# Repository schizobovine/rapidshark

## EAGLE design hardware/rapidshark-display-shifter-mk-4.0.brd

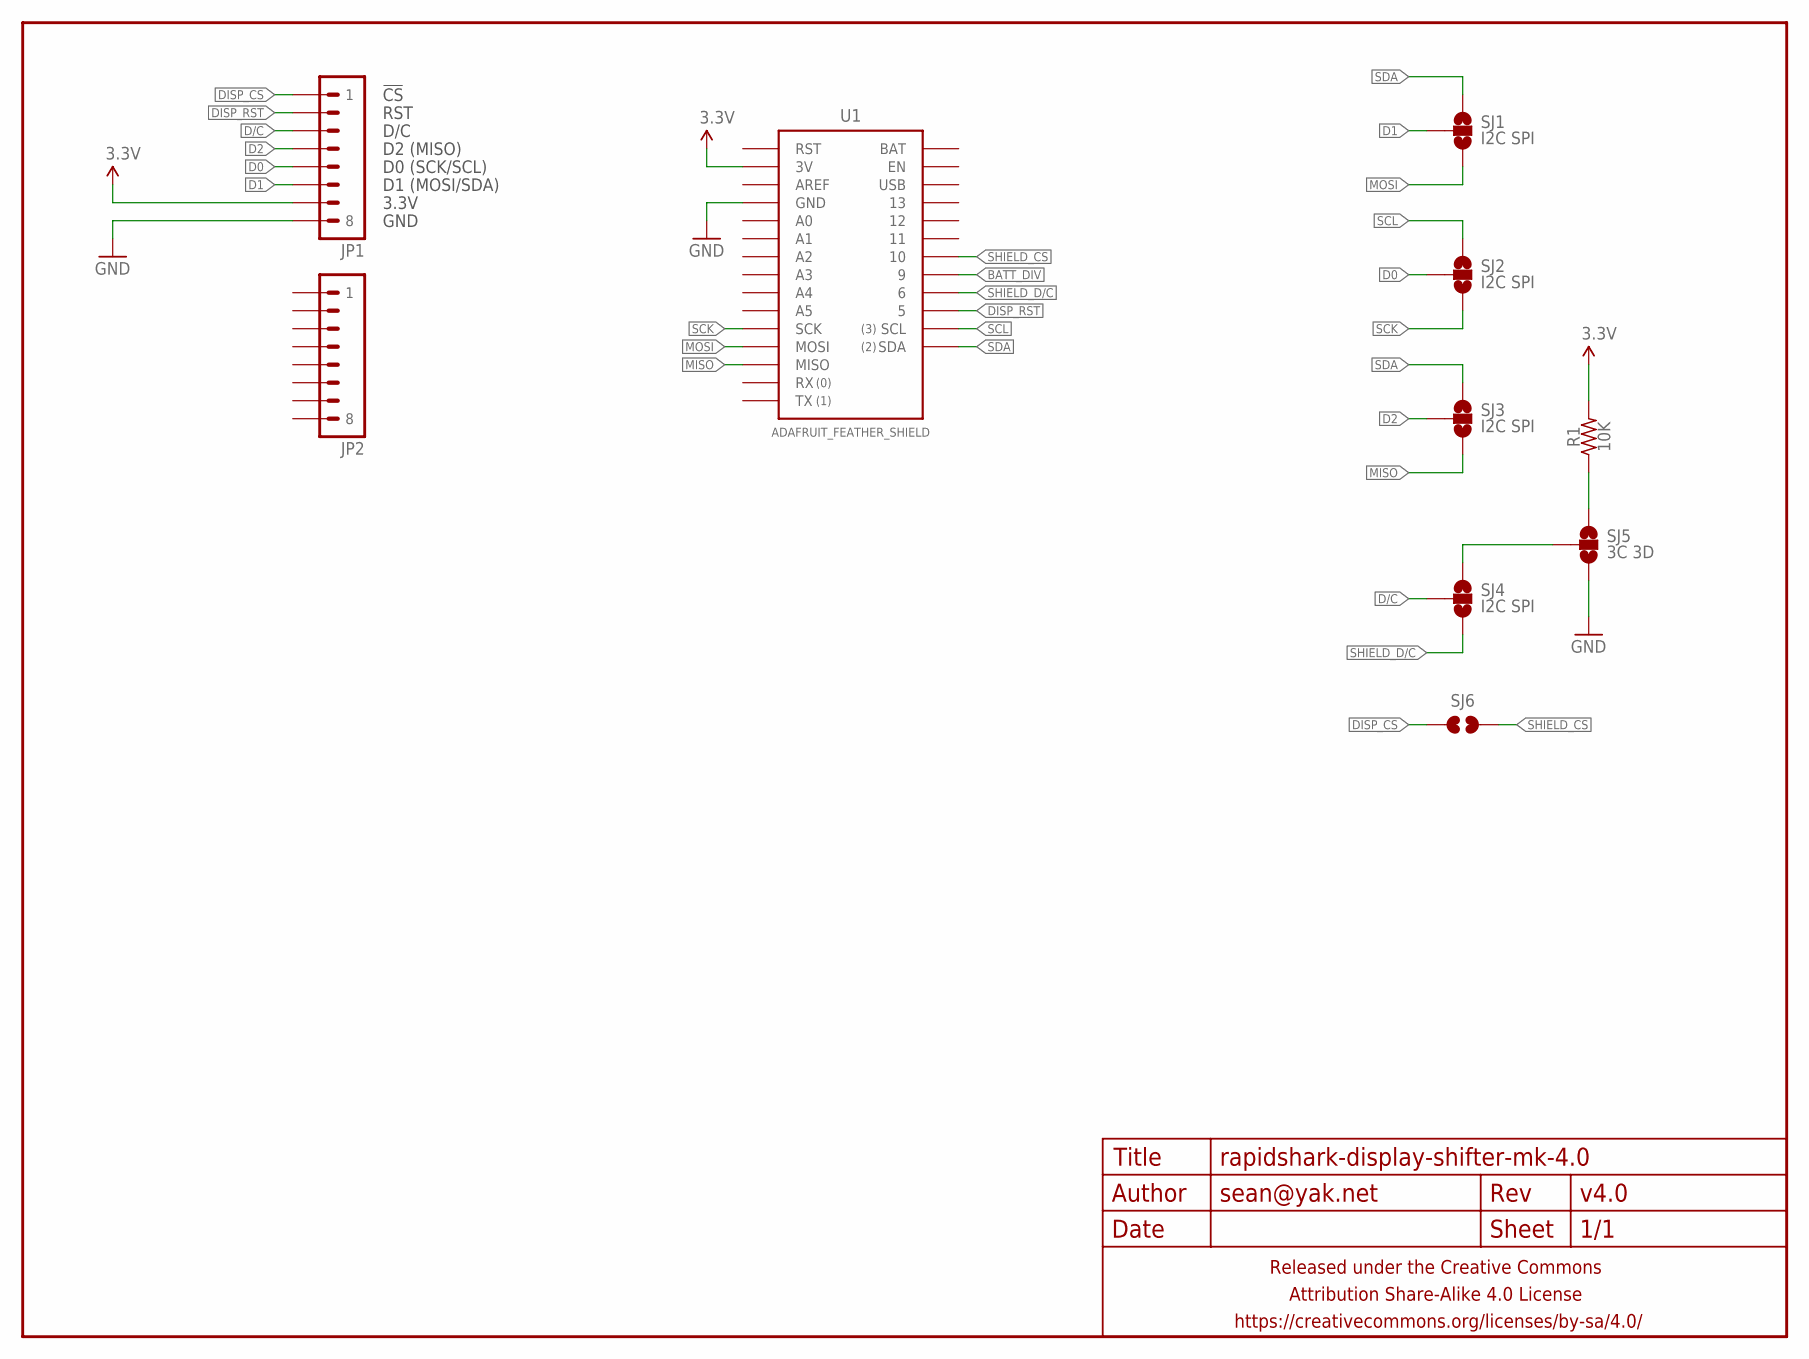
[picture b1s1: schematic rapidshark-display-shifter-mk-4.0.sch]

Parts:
FRAME1: FRAME-LETTERNO_PACKAGE; DUMMY
JP1, JP2: M081X08; 1X08
R1: 10K; R0603
SJ1, SJ2, SJ3, SJ4: I2C SPI; PAD-JUMPER-3-NO_YES_SILK_FULL_BOX
SJ5: 3C 3D; PAD-JUMPER-3-NO_YES_SILK_FULL_BOX
SJ6: JUMPER-PAD-2-NOYES_SILK; PAD-JUMPER-2-NO_YES_SILK
U1: ADAFRUIT_FEATHER_SHIELD; ADAFRUIT_FEATHER

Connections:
3.3V: JP1.7, R1.2, U1.3V
BATT_DIV: U1.9
D0: JP1.5, SJ2.2
D1: JP1.6
D2: JP1.4
D/C: JP1.3
DISP_CS: JP1.1, SJ6.1
DISP_RST: JP1.2, U1.5
GND: JP1.8, SJ5.3, U1.GND@0 (GND), U1.GND@1 (GND)
MISO: SJ3.3, U1.MISO
MOSI: SJ1.3, U1.MOSI
unnamed: R1.1, SJ5.1
unnamed: SJ4.1, SJ5.2
SCK: SJ2.3, U1.SCK
SCL: SJ2.1, U1.SCL
SDA: SJ1.1, U1.SDA
SHIELD_CS: SJ6.2, U1.10
SHIELD_D/C: SJ4.3, U1.6

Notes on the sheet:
GND
3.3V
D1 (MOSI/SDA)
D0 (SCK/SCL)
D2 (MISO)
D/C
RST
!CS

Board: 2 copper layers, 13 parts (3 on the bottom side), 14 nets, no tracks yet.

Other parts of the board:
U$1: COW_SMALL
U$3: OSHWLOGO_TINY_SILKONLY

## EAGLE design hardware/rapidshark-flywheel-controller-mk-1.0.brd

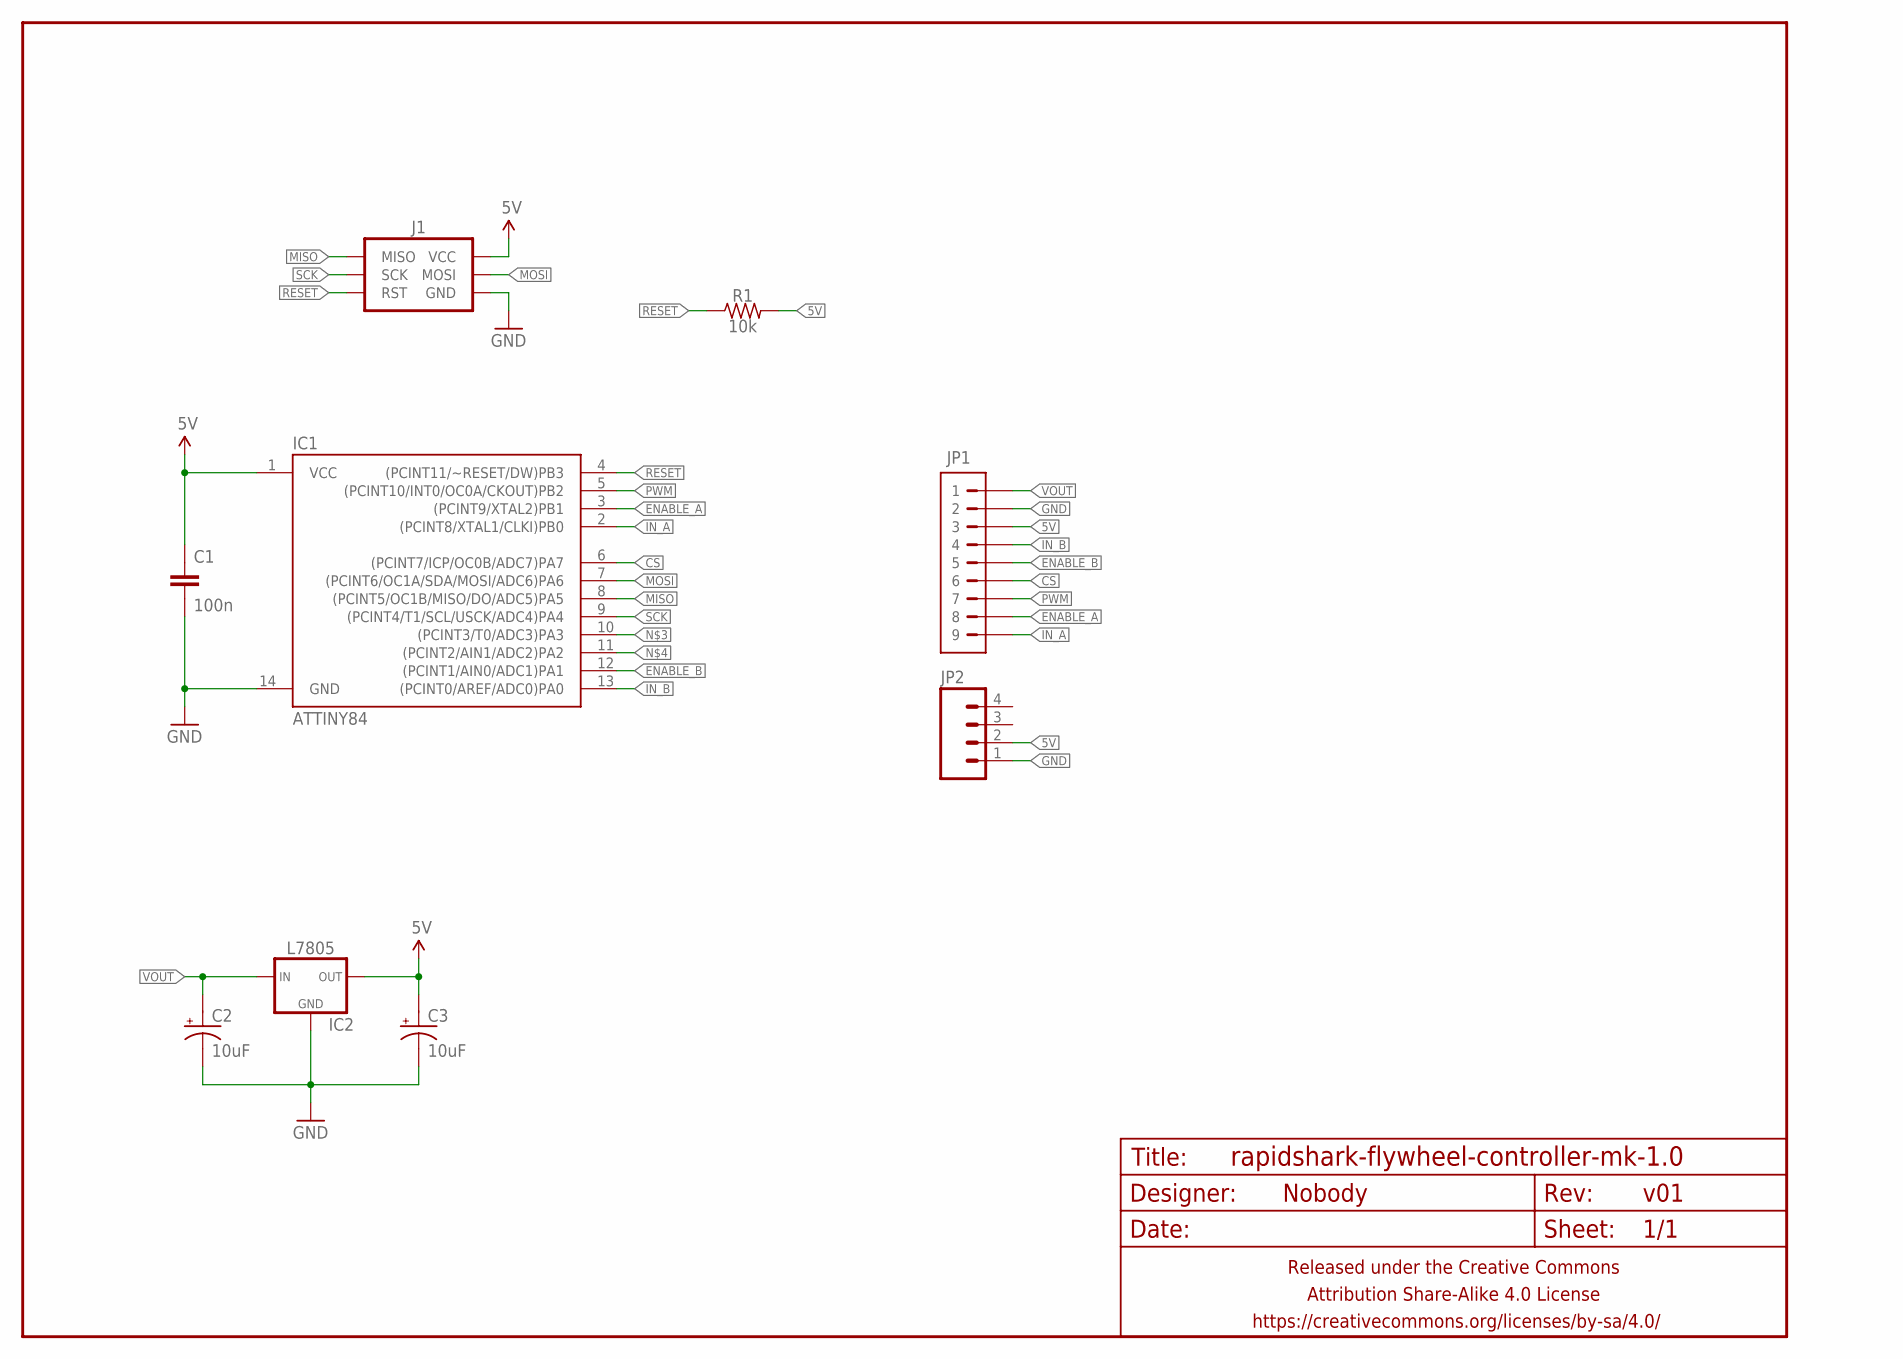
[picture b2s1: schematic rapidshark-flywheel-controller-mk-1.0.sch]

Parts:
C1: 100n; C0805
C2, C3: 10uF; E2-5
FRAME1: FRAME-LETTERNO_PACKAGE; DUMMY
IC1: ATTINY84; SO14
IC2: L7805; TO-92-AMMO
J1: AVR_SPI_PRG_6PTH; 2X3
JP1: M09CENTERED; 1X09-CENTERED
JP2: M04JST-PTH-VERT; JST-4-PH-VERT-PTH
R1: 10k; R0805

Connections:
5V: C1.1, C3.+, IC1.1 (VCC), IC2.3 (OUT), J1.2 (VCC), JP1.3, JP2.2, R1.2
CS: IC1.6 ((PCINT7/ICP/OC0B/ADC7)PA7), JP1.6
ENABLE_A: IC1.3 ((PCINT9/XTAL2)PB1), JP1.8
ENABLE_B: IC1.12 ((PCINT1/AIN0/ADC1)PA1), JP1.5
GND: C1.2, C2.-, C3.-, IC1.14 (GND), IC2.2 (GND), J1.6 (GND), JP1.2, JP2.1
IN_A: IC1.2 ((PCINT8/XTAL1/CLKI)PB0), JP1.9
IN_B: IC1.13 ((PCINT0/AREF/ADC0)PA0), JP1.4
MISO: IC1.8 ((PCINT5/OC1B/MISO/DO/ADC5)PA5), J1.1 (MISO)
MOSI: IC1.7 ((PCINT6/OC1A/SDA/MOSI/ADC6)PA6), J1.4 (MOSI)
PWM: IC1.5 ((PCINT10/INT0/OC0A/CKOUT)PB2), JP1.7
RESET: IC1.4 ((PCINT11/~RESET/DW)PB3), J1.5 (RST), R1.1
SCK: IC1.9 ((PCINT4/T1/SCL/USCK/ADC4)PA4), J1.3 (SCK)
VOUT: C2.+, IC2.1 (IN), JP1.1

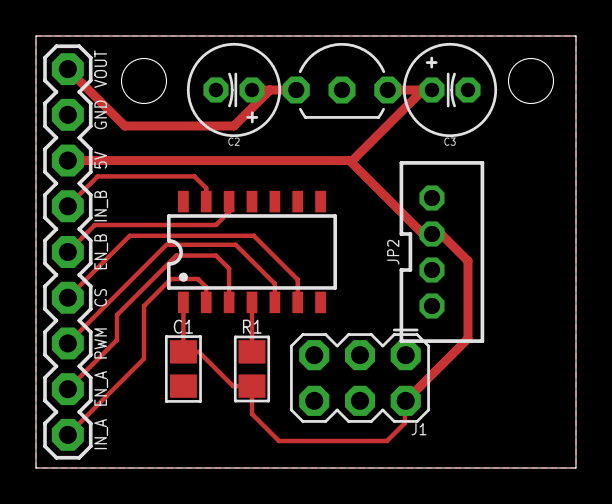
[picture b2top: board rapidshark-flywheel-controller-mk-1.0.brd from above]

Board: 2 copper layers, 30.0 x 24.0 mm, 10 parts (1 on the bottom side), 13 nets.

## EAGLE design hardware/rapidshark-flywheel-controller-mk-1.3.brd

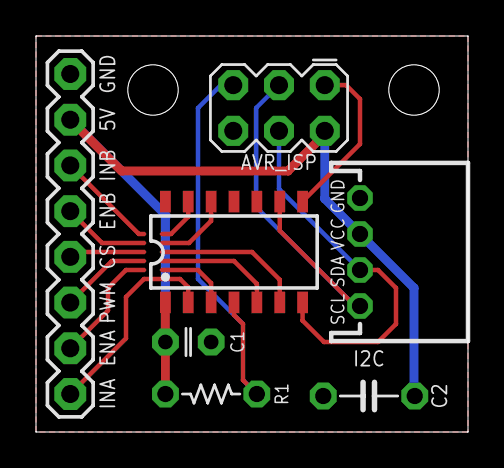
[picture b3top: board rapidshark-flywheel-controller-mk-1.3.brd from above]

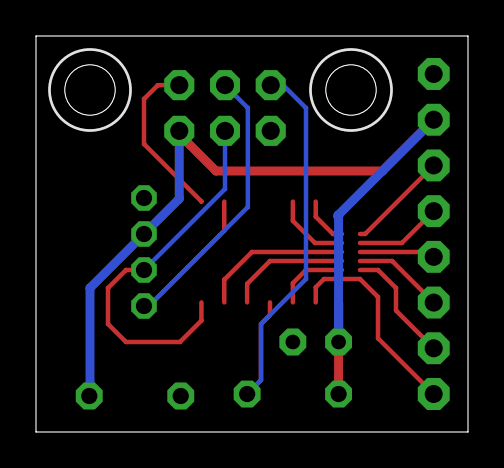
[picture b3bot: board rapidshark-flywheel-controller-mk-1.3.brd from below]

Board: 2 copper layers, 24.0 x 22.0 mm, 11 parts (4 on the bottom side), 12 nets.

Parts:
AVR_ISP: AVR_SPI_PRG_6PTH; 2X3
C1: 100n; CAPCER-RAD-PTH-2.54MM
C2: 10u; CAPCER-RAD-PTH-5.08MM
FRAME1: FRAME-LETTERNO_PACKAGE; DUMMY
I2C: M04-I2CJST-4-PH-RA-CENTERED; 1X04-JST-PH-RA-PTH-I2C-CENTERED
IC1: ATTINY84; SO14
JP1: 1X08
R1: 10k; RESISTOR-AXIAL-PTH-5.08MM
U$1: CC-BY-SA-4.0-NO-URL
U$2: COW_SMALL_METAL
U$3: OSHWLOGO_TOP_0.2

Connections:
5V: AVR_ISP.2, C1.1, C2.1, I2C.2, IC1.1, JP1.2, R1.P$2
CS: IC1.6, JP1.5
ENABLE_A: IC1.3, JP1.7
ENABLE_B: IC1.12, JP1.4
GND: AVR_ISP.6, C1.2, C2.2, I2C.1, IC1.14, JP1.1
IN_A: IC1.2, JP1.8
IN_B: IC1.13, JP1.3
MISO: AVR_ISP.1, IC1.8
MOSI/SDA: AVR_ISP.4, I2C.3, IC1.7
PWM: IC1.5, JP1.6
RESET: AVR_ISP.5, IC1.4, R1.P$1
SCK/SCL: AVR_ISP.3, I2C.4, IC1.9

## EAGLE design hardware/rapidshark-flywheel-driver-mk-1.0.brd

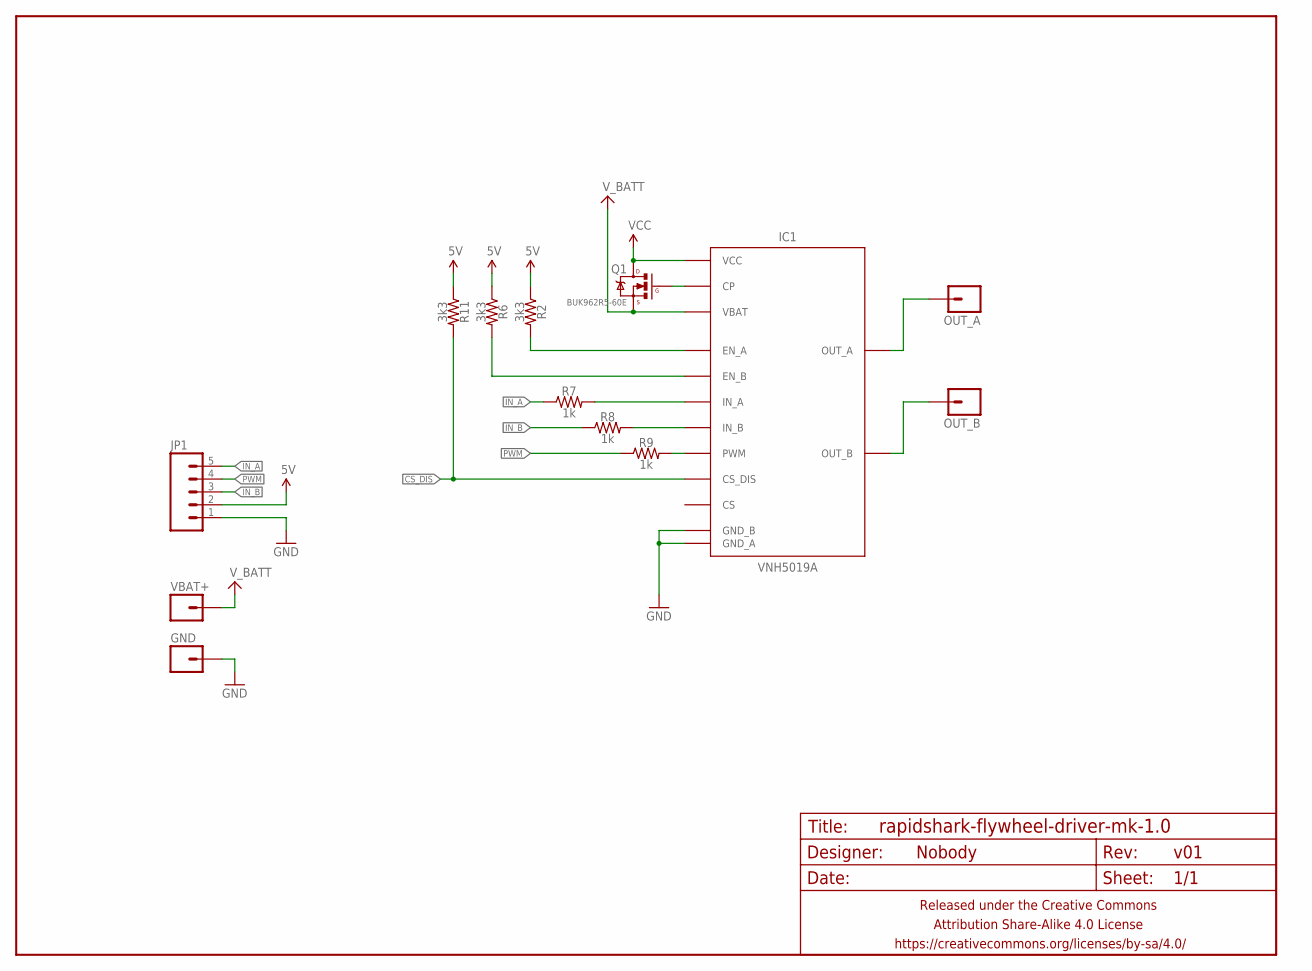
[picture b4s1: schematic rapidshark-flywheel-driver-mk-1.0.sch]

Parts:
FRAME1: FRAME-LETTERNO_PACKAGE; DUMMY
GND: M0112AWG; 1X01-12AWG
IC1: VNH5019A
JP1: M05JST-PH-RA-PTH; JST-5-PH-RA-PTH
OUT_A: M0112AWG; 1X01-12AWG
OUT_B: M0112AWG; 1X01-12AWG
Q1: BUK962R5-60E; SOT-669
R2, R6, R11: 3k3; R0603
R7, R8, R9: 1k; R0603
VBAT+: M0112AWG; 1X01-12AWG

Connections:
5V: JP1.2, R2.1, R6.1, R11.1
CS_DIS: IC1.6 (CS_DIS), R11.2
EN_A1: IC1.5 (EN_A), R2.2
EN_B1: IC1.9 (EN_B), R6.2
GATE: IC1.11 (CP), Q1.4 (G)
GND: GND.1, IC1.17 (GND_A), IC1.18 (GND_B), IC1.19 (GND_B), IC1.20 (GND_B), IC1.26 (GND_A), IC1.27 (GND_A), IC1.28 (GND_A), IC1.29 (GND_A), JP1.1
IN_A: JP1.5, R7.1
IN_A1: IC1.4 (IN_A), R7.2
IN_B: JP1.3, R8.1
IN_B1: IC1.10 (IN_B), R8.2
OUT_A: IC1.1 (OUT_A), IC1.24 (OUT_A), IC1.25 (OUT_A), IC1.30 (OUT_A), IC1.HS2 (OUT_A), OUT_A.1
OUT_B: IC1.15 (OUT_B), IC1.16 (OUT_B), IC1.21 (OUT_B), IC1.22 (OUT_B), IC1.HS3 (OUT_B), OUT_B.1
PWM: JP1.4, R9.1
PWM1: IC1.7 (PWM), R9.2
VCC: IC1.2 (VCC), IC1.3 (VCC), IC1.13 (VCC), IC1.14 (VCC), IC1.23 (VCC), IC1.HS1 (VCC), Q1.5 (D)
V_BATT: IC1.12 (VBAT), Q1.1 (S), Q1.2 (S), Q1.3 (S), VBAT+.1

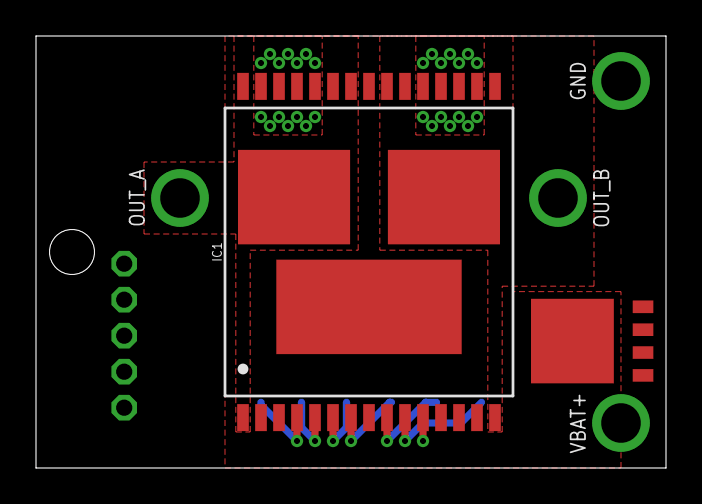
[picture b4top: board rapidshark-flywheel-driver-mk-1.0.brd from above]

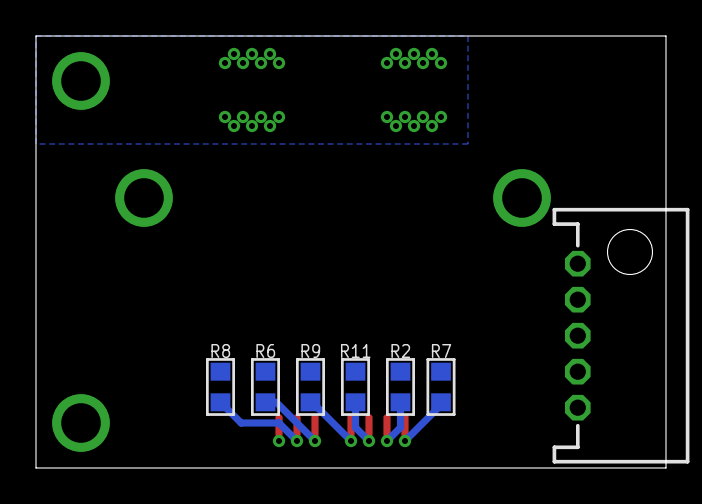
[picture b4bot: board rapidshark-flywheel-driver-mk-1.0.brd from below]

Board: 2 copper layers, 35.0 x 24.0 mm, 14 parts (8 on the bottom side), 16 nets.

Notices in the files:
parts and their libraries:
A_butts: Released under the Creative Commons Attribution Share-Alike 4.0 License
A_butts: https://creativecommons.org/licenses/by-sa/4.0
A_butts: Released under the Creative Commons
